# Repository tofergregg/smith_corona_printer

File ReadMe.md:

# Smith Corona Typewriter to Printer Project
This project aims to convert a 1960s Smith Corona Sterling Automatic 12
typewriter into a printer using solenoids, circuits, and code.

To set up midi:

1. Open Hairless-MIDI Serial Bridge
2. Connect Serial port to USB (may be "USB ACM" for Genuine Arduino)
3. Should have MIDI In set to "IAC Driver Bus 1" and MIDI Out set to "(Not Connected)"
4. Open Melody Assistant
5. Instruments->Relate Output Device, set Helicopter and Car Engine to MIDI 1
6. If necessary, test MIDI output with Configuration->MIDI Configuration,
   MIDI output 1 should be set to Bus 1, and then Test
7. Set to 115,200 Baud, N81
8. For actualTypewriter.py: need to pip install python-rtmidi (and others)

Correct Arduino file: TypewriterSongMIDI2

Song for Melody Assistant: typewriterFluteHighQ2_typewriter.myr

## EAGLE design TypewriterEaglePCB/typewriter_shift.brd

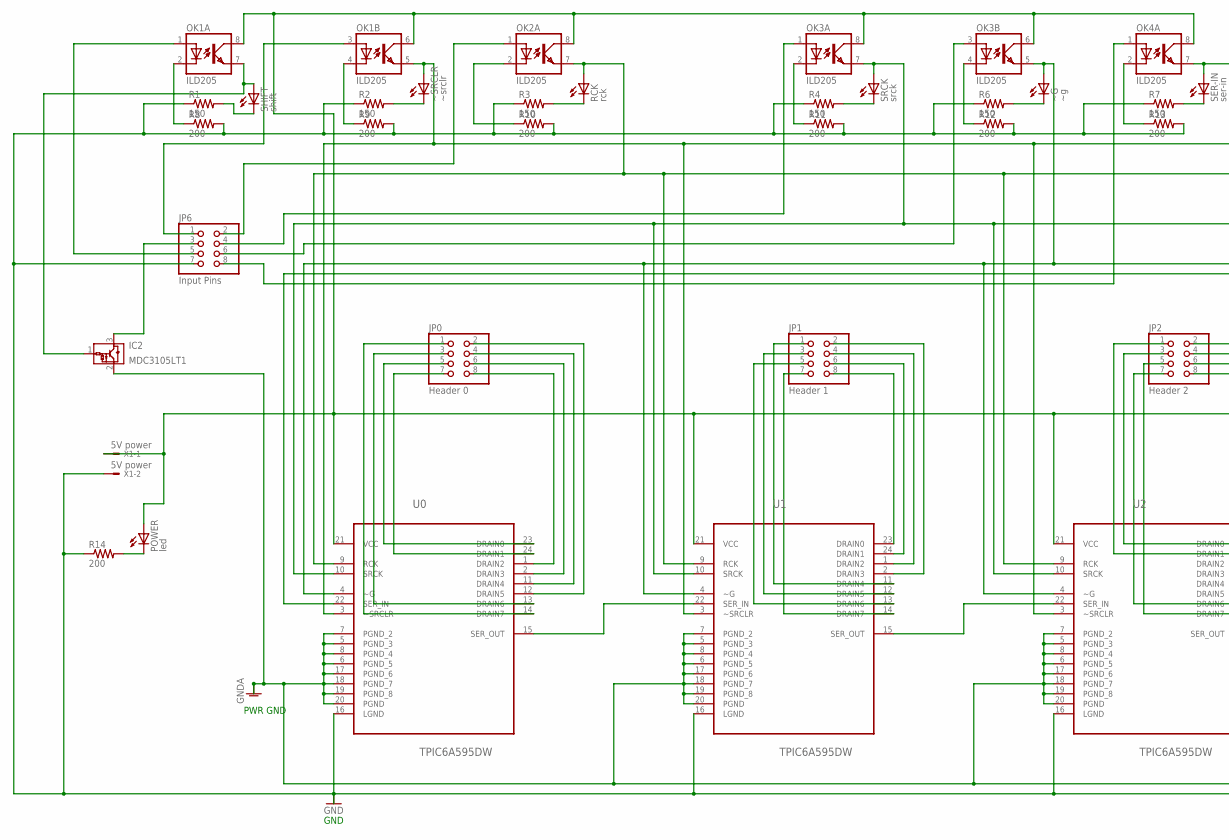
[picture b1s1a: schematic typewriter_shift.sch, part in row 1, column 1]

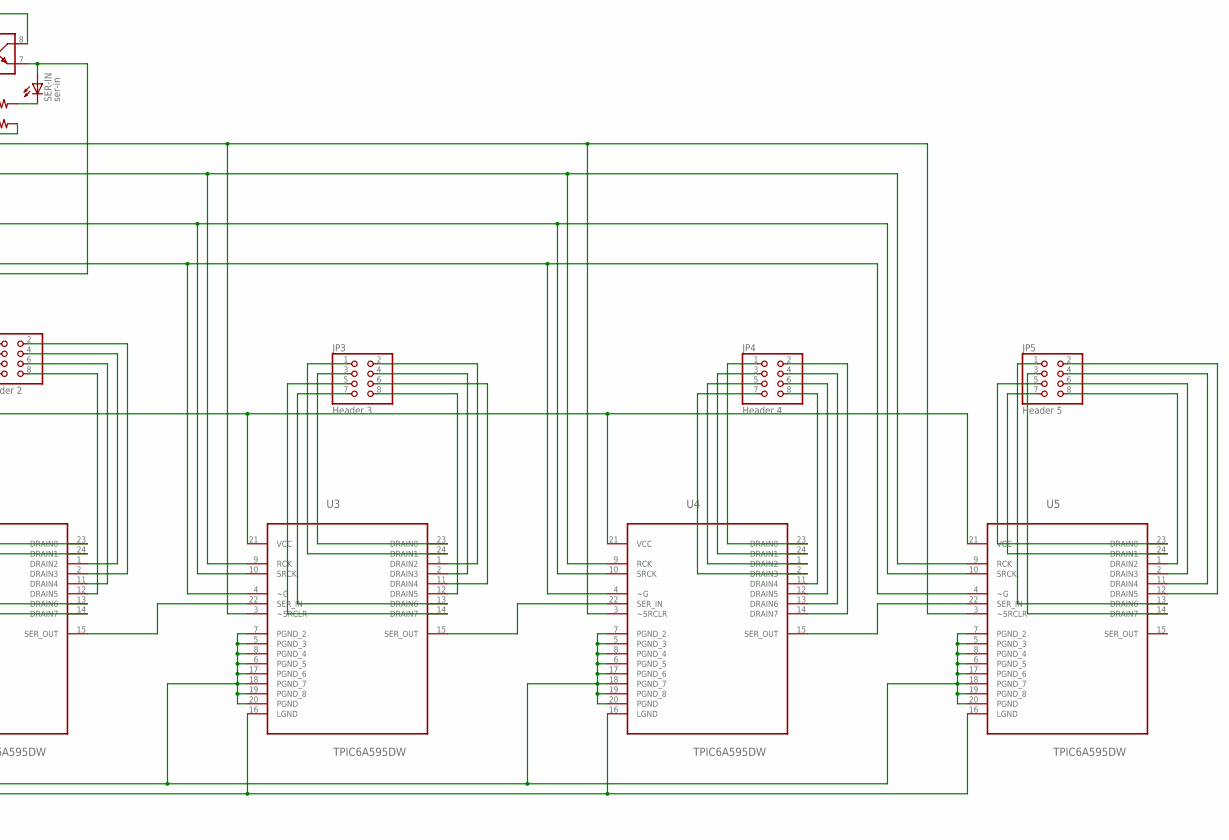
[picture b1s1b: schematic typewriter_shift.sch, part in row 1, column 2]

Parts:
IC2: MDC3105LT1; SOT23
JP0: Header 0; 2X04/90
JP1: Header 1; 2X04/90
JP2: Header 2; 2X04/90
JP3: Header 3; 2X04/90
JP4: Header 4; 2X04/90
JP5: Header 5; 2X04/90
JP6: Input Pins; 2X04/90
OK1, OK2, OK3, OK4: ILD205; SOIC08
POWER: led; SML1206
R1, R2, R3, R4, R6, R7: 150; R1206
R8, R9, R10, R11, R12, R13, R14: 200; R1206
RCK: rck; SML1206
SER-IN: ser-in; SML1206
SHIFT: shift; SML1206
SRCK: srck; SML1206
U0, U1, U2, U3, U4, U5: TPIC6A595DW; SOIC127P1030X265-24N
X1: 5V power; KK-156-2
~G: ~g; SML1206
~SRCLR: ~srclr; SML1206

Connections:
GND: JP6.7, R1.1, R2.1, R3.1, R4.1, R6.1, R7.1, R8.2, R9.2, R10.2, R11.2, R12.2, R13.2, R14.1, U0.16 (LGND), U1.16 (LGND), U2.16 (LGND), U3.16 (LGND), U4.16 (LGND), U5.16 (LGND), X1.2
GNDA: IC2.2 (GND), U0.5 (PGND_3), U0.6 (PGND_5), U0.7 (PGND_2), U0.8 (PGND_4), U0.17 (PGND_6), U0.18 (PGND_7), U0.19 (PGND_8), U0.20 (PGND), U1.5 (PGND_3), U1.6 (PGND_5), U1.7 (PGND_2), U1.8 (PGND_4), U1.17 (PGND_6), U1.18 (PGND_7), U1.19 (PGND_8), U1.20 (PGND), U2.5 (PGND_3), U2.6 (PGND_5), U2.7 (PGND_2), U2.8 (PGND_4), U2.17 (PGND_6), U2.18 (PGND_7), U2.19 (PGND_8), U2.20 (PGND), U3.5 (PGND_3), U3.6 (PGND_5), U3.7 (PGND_2), U3.8 (PGND_4), U3.17 (PGND_6), U3.18 (PGND_7), U3.19 (PGND_8), U3.20 (PGND), U4.5 (PGND_3), U4.6 (PGND_5), U4.7 (PGND_2), U4.8 (PGND_4), U4.17 (PGND_6), U4.18 (PGND_7), U4.19 (PGND_8), U4.20 (PGND), U5.5 (PGND_3), U5.6 (PGND_5), U5.7 (PGND_2), U5.8 (PGND_4), U5.17 (PGND_6), U5.18 (PGND_7), U5.19 (PGND_8), U5.20 (PGND)
unnamed: U0.15 (SER_OUT), U1.22 (SER_IN)
unnamed: U1.15 (SER_OUT), U2.22 (SER_IN)
unnamed: U2.15 (SER_OUT), U3.22 (SER_IN)
unnamed: U3.15 (SER_OUT), U4.22 (SER_IN)
unnamed: U4.15 (SER_OUT), U5.22 (SER_IN)
unnamed: R3.2, RCK.C
unnamed: OK4.7 (EMIT), SER-IN.A, U0.22 (SER_IN)
unnamed: R2.2, ~SRCLR.C
unnamed: JP0.7, U0.24 (DRAIN1)
unnamed: JP6.5, OK1.1 (A)
unnamed: JP0.5, U0.23 (DRAIN0)
unnamed: JP0.8, U0.1 (DRAIN2)
unnamed: JP0.6, U0.2 (DRAIN3)
unnamed: IC2.3 (VOUT), JP6.3
unnamed: IC2.1 (VIN), OK1.7 (EMIT), SHIFT.A
unnamed: OK1.2 (C), R8.1
unnamed: JP0.4, U0.11 (DRAIN4)
unnamed: JP0.2, U0.12 (DRAIN5)
unnamed: JP6.1, OK1.3 (A)
unnamed: JP0.3, U0.13 (DRAIN6)
unnamed: JP0.1, U0.14 (DRAIN7)
unnamed: JP6.2, OK2.1 (A)
unnamed: JP1.4, U1.1 (DRAIN2)
unnamed: JP1.6, U1.24 (DRAIN1)
unnamed: JP1.8, U1.23 (DRAIN0)
unnamed: JP1.2, U1.2 (DRAIN3)
unnamed: JP1.1, U1.11 (DRAIN4)
unnamed: JP6.4, OK3.1 (A)
unnamed: JP6.8, OK4.1 (A)
unnamed: JP6.6, OK3.3 (A)
unnamed: OK3.4 (C), R12.1
unnamed: JP1.7, U1.14 (DRAIN7)
unnamed: JP1.3, U1.12 (DRAIN5)
unnamed: JP1.5, U1.13 (DRAIN6)
unnamed: JP3.3, U3.23 (DRAIN0)
unnamed: JP2.6, U2.11 (DRAIN4)
unnamed: JP2.4, U2.1 (DRAIN2)
unnamed: JP2.2, U2.2 (DRAIN3)
unnamed: JP2.5, U2.14 (DRAIN7)
unnamed: JP2.7, U2.13 (DRAIN6)
unnamed: JP2.3, U2.23 (DRAIN0)
unnamed: JP2.1, U2.24 (DRAIN1)
unnamed: JP2.8, U2.12 (DRAIN5)
unnamed: JP3.1, U3.24 (DRAIN1)
unnamed: JP3.2, U3.1 (DRAIN2)
unnamed: JP3.4, U3.2 (DRAIN3)
unnamed: JP3.6, U3.11 (DRAIN4)
unnamed: JP3.8, U3.12 (DRAIN5)
unnamed: JP3.7, U3.13 (DRAIN6)
unnamed: JP3.5, U3.14 (DRAIN7)
unnamed: JP4.1, U4.23 (DRAIN0)
unnamed: JP4.3, U4.24 (DRAIN1)
unnamed: JP4.5, U4.1 (DRAIN2)
unnamed: JP4.7, U4.2 (DRAIN3)
unnamed: JP4.8, U4.11 (DRAIN4)
unnamed: JP4.6, U4.12 (DRAIN5)
unnamed: JP4.4, U4.13 (DRAIN6)
unnamed: JP4.2, U4.14 (DRAIN7)
unnamed: JP5.5, U5.23 (DRAIN0)
unnamed: JP5.7, U5.24 (DRAIN1)
unnamed: JP5.8, U5.1 (DRAIN2)
unnamed: JP5.6, U5.2 (DRAIN3)
unnamed: JP5.4, U5.11 (DRAIN4)
unnamed: JP5.2, U5.12 (DRAIN5)
unnamed: JP5.1, U5.13 (DRAIN6)
unnamed: JP5.3, U5.14 (DRAIN7)
unnamed: OK3.5 (EMIT), U0.4 (~G), U1.4 (~G), U2.4 (~G), U3.4 (~G), U4.4 (~G), U5.4 (~G), ~G.A
unnamed: OK3.7 (EMIT), SRCK.A, U0.10 (SRCK), U1.10 (SRCK), U2.10 (SRCK), U3.10 (SRCK), U4.10 (SRCK), U5.10 (SRCK)
unnamed: OK2.7 (EMIT), RCK.A, U0.9 (RCK), U1.9 (RCK), U2.9 (RCK), U3.9 (RCK), U4.9 (RCK), U5.9 (RCK)
unnamed: OK1.5 (EMIT), U0.3 (~SRCLR), U1.3 (~SRCLR), U2.3 (~SRCLR), U3.3 (~SRCLR), U4.3 (~SRCLR), U5.3 (~SRCLR), ~SRCLR.A
unnamed: OK4.2 (C), R13.1
unnamed: R1.2, SHIFT.C
unnamed: R4.2, SRCK.C
unnamed: R6.2, ~G.C
unnamed: OK3.2 (C), R11.1
unnamed: OK2.2 (C), R10.1
unnamed: OK1.4 (C), R9.1
unnamed: R7.2, SER-IN.C
unnamed: POWER.C, R14.2
VCC: OK1.6 (COL), OK1.8 (COL), OK2.8 (COL), OK3.6 (COL), OK3.8 (COL), OK4.8 (COL), POWER.A, U0.21 (VCC), U1.21 (VCC), U2.21 (VCC), U3.21 (VCC), U4.21 (VCC), U5.21 (VCC), X1.1

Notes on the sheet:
GND
PWR GND

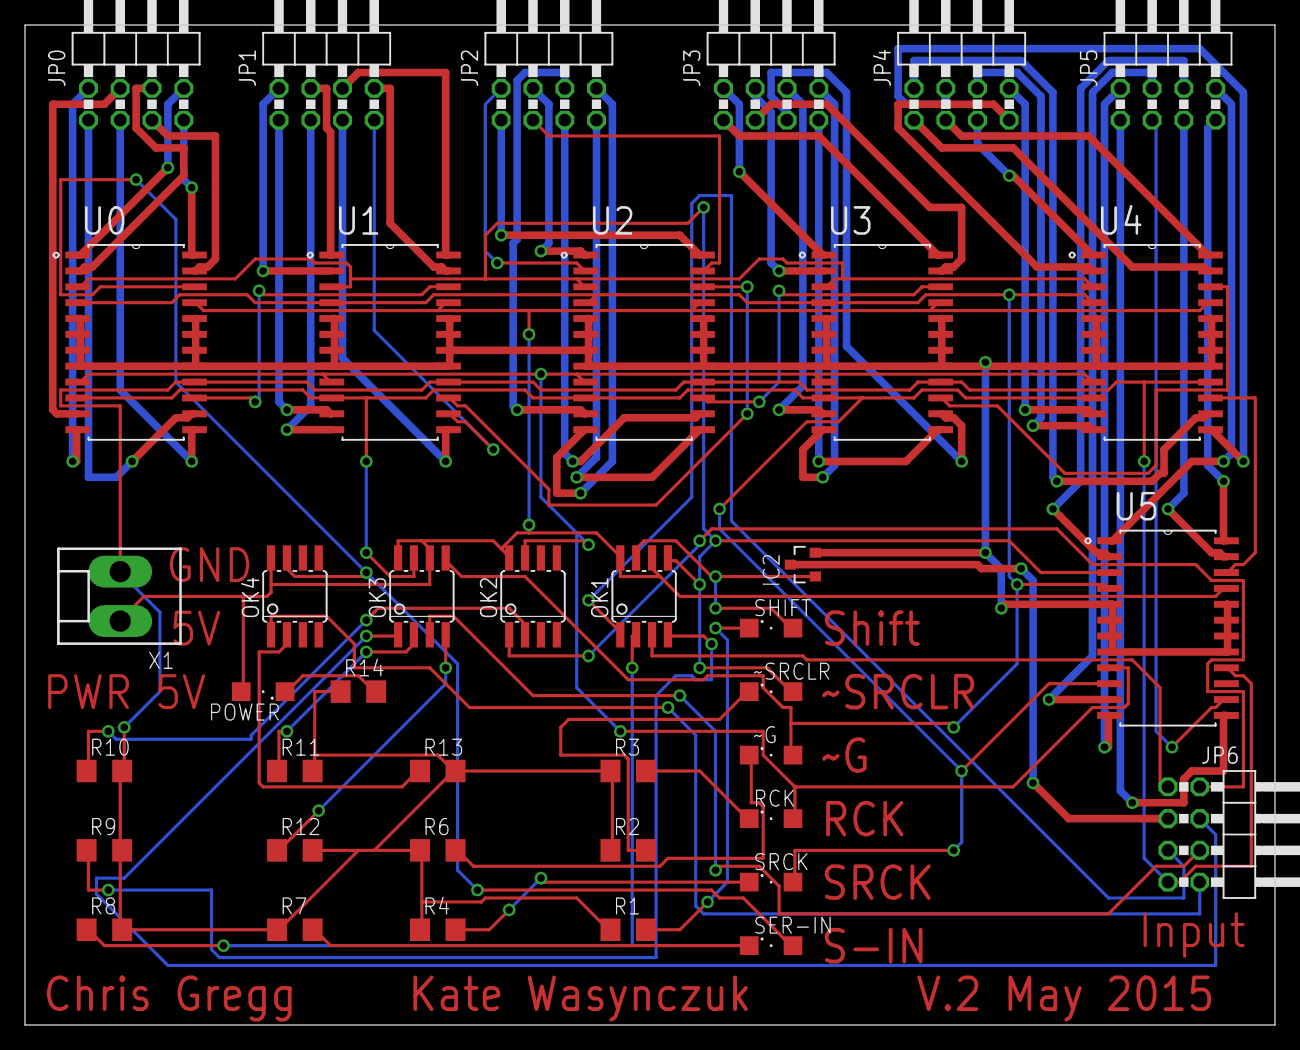
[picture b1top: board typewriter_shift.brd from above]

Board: 2 copper layers, 100.0 x 80.0 mm, 39 parts (0 on the bottom side), 82 nets.

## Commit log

2015-05-10 Updated README.md to discuss typewriter
2015-05-10 TypewriterBeanOSX
2015-05-10 updated name for PCB directory
2015-05-10 had to rename arduino file so it matched the folder name...
2015-05-10 Fixed spelling mistake on folder name
2015-05-10 Updated eagle files
2015-05-10 Updated directory to match style
2015-05-10 Added ReadMe.md
2015-05-11 latest update with resistors and LEDs
2015-05-11 Updated circuit with correct resistances for optoisolators and LEDs
2015-05-11 Added wide power ground traces and 1206 resistors
2015-05-23 Updated Bean code and OS X code
2015-05-23 Added shift code to Arduino
2015-05-23 Added a queue for serial data transfers
2015-05-23 Took out commented delays
2015-05-24 Updated OS X Bean code to send actual characters
2015-05-24 Revamped Arduino code to send actual characters
2015-05-24 Added most character codes to Arduino.
2015-05-24 Added full text box to OS X code
2015-05-24 Updated inital character mappings on Arduino
2015-05-24 Added string cleaner for only typewriter-allowed characters
2015-05-28 Lots of Bean changes
2015-05-28 Lots of OS X Bean changes
2015-05-28 not sure what eagle changes there were...
2015-05-28 Initial CUPS printer driver commit
2015-05-28 Playing around with clocks
2015-05-28 added replacement for elipses
2015-05-30 Added capslock and shift to Arduino; fixed up lots of little errors. Also added exclamation point, which is an apostrophe-backspace-period
2015-05-30 Added more translations
2015-05-31 accidentally had svn files in repo--removed
2015-05-31 added SmithCoronaDriver
2015-05-31 removed some old driver info
2015-05-31 renamed driver with CUPS identifier
2015-06-01 Added longer delay for CAPS lock key
2015-06-01 changed pbxproj file to put files into the correct path
2015-06-01 Initial commit for Bean CUPS driver
2015-06-02 updated CUPS driver to handle then not handle being a printer driver. Can't figure out how to get the driver to run as a standalone program, nor how to actually use the windows (e.g., you can't type 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
2015-06-02 updated original driver with smithcorona names
2015-06-02 After breaking the circuit and fixing it with new chips, we are back to a regular layout for the keys - e.g., no more jumping a spot due to a wonky first or second shift register.
2015-06-21 Added Arduino Serial port files
2015-06-22 Added ORSSerialPortManager files
2015-06-25 Updated Typewriter Bean sketch to include the bell.
2015-06-25 Added Typewriter Song sketch
2015-06-25 Added Lasercutter template and MIDI files
2015-06-25 instruments file was huge, so I deleted it.
2015-06-25 Updated keyboard template for second shift key hole
2015-06-30 Updated Arduino code for bell
2015-06-30 Minor changes to OS X app
2015-07-01 Completely changed song sketch to use proper MIDI input
2015-07-01 Minor changes to OS X program
2015-07-01 Added a MIDI file with the bell and Carriage Return tracks in the Flute track
2015-07-01 Made the typewriter a bit faster
2015-07-21 Added new Arduino MIDI sketch
2015-07-21 Updated original MIDI arduino sketch
2016-04-13 Updated ReadMe.md for MIDI instructions
2017-01-02 updated actualTypewriter.py to find correct MIDI
